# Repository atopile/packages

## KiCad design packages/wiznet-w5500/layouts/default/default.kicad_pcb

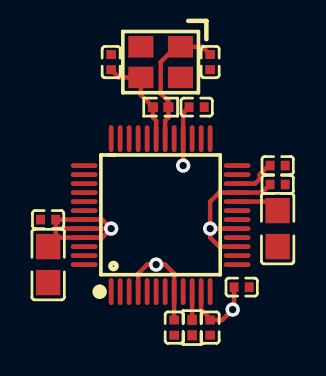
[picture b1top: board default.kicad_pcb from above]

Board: 2 copper layers, 15 parts (0 on the bottom side), 7 nets.

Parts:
C1, C9: 0F; C0805
C2, C3, C4, C5, C6, C7, C8, C10, C11: 0F; C0402
R1: 12400Ω; R0402
R2: 1000000Ω; R0402
U1: LQFP-48_L7.0-W7.0-P0.50-LS9.0-BL
X1: OSC-SMD_4P-L3.2-W2.5-BL_SIT8008BI

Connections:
10: R1.1, U1.10
hv: C1.1, C2.1, C3.1, C4.1, C5.1, C6.1, C7.1, U1.4, U1.8, U1.11, U1.15, U1.17, U1.21, U1.28, U1.43, U1.44, U1.45
lv: C1.2, C2.2, C3.2, C4.2, C5.2, C6.2, C7.2, C8.2, C9.2, C10.2, C11.2, R1.2, U1.3, U1.9, U1.14, U1.16, U1.19, U1.29, U1.48, X1.2, X1.4
p1v2o_cap-power-hv: C8.1, U1.22
tocap_cap-power-hv: C9.1, U1.20
xtal_caps[0]-power-hv: C10.1, R2.1, U1.30, X1.1
xtal_caps[1]-power-hv: C11.1, R2.2, U1.31, X1.3

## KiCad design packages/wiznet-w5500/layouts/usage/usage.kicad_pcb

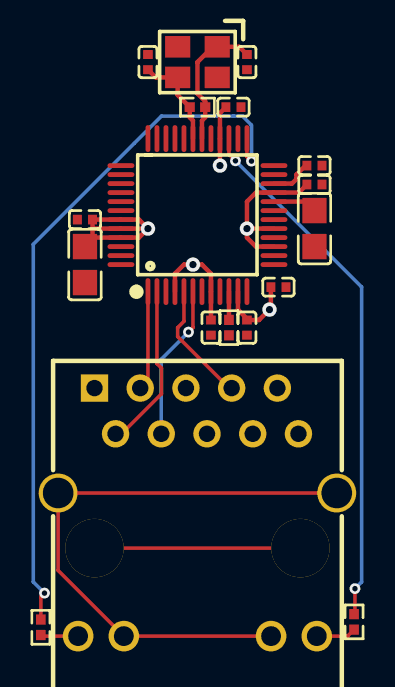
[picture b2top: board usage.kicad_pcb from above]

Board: 2 copper layers, 18 parts (0 on the bottom side), 15 nets.

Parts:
C1, C9: 0F; C0805
C2, C3, C4, C5, C6, C7, C8, C10, C11: 0F; C0402
R1: 12400Ω; R0402
R2: 1000000Ω; R0402
R3, R4: 470Ω; R0402
RJ1: RJ45-TH_HR911130A
U1: LQFP-48_L7.0-W7.0-P0.50-LS9.0-BL
X1: OSC-SMD_4P-L3.2-W2.5-BL_SIT8008BI

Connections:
10: R1.1, U1.10
11: R4.2, RJ1.11
14: R3.2, RJ1.14
W5500_ACT_LED: R3.1, U1.27
W5500_LINK_LED: R4.1, U1.25
W5500_RXN_N: RJ1.P7, U1.5
W5500_RXP_P: RJ1.P4, U1.6
W5500_TXN_N: RJ1.P3, U1.1
W5500_TXP_P: RJ1.P2, U1.2
hv: C1.1, C2.1, C3.1, C4.1, C5.1, C6.1, C7.1, U1.4, U1.8, U1.11, U1.15, U1.17, U1.21, U1.28, U1.43, U1.44, U1.45
lv: C1.2, C2.2, C3.2, C4.2, C5.2, C6.2, C7.2, C8.2, C9.2, C10.2, C11.2, R1.2, RJ1.12, RJ1.13, RJ1.SHIELD0, RJ1.SHIELD1, U1.3, U1.9, U1.14, U1.16, U1.19, U1.29, U1.48, X1.2, X1.4
p1v2o_cap-power-hv: C8.1, U1.22
tocap_cap-power-hv: C9.1, U1.20
xtal_caps[0]-power-hv: C10.1, R2.1, U1.30, X1.1
xtal_caps[1]-power-hv: C11.1, R2.2, U1.31, X1.3

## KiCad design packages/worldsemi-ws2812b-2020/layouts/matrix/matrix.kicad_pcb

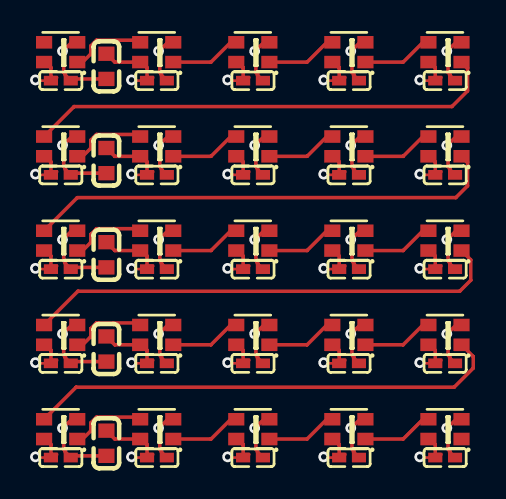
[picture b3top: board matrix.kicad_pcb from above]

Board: 2 copper layers, 55 parts (0 on the bottom side), 26 nets.

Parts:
C1, C7, C13, C19, C25: 10µF ±20% 6.3V X5R; C0603
C2, C3, C4, C5, C6, C8, C9, C10, C11, C12, C14, C15, C16, C17, C18, C20, C21, C22, C23, C24, C26, C27, C28, C29, C30: 100nF ±10% 16V X7R; C0402
LED1, LED2, LED3, LED4, LED5, LED6, LED7, LED8, LED9, LED10, LED11, LED12, LED13, LED14, LED15, LED16, LED17, LED18, LED19, LED20, LED21, LED22, LED23, LED24, LED25: LED-SMD_4P-L2.0-W2.0-TL_WS2812B-2020

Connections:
GND: C1.2, C2.2, C3.2, C4.2, C5.2, C6.2, C7.2, C8.2, C9.2, C10.2, C11.2, C12.2, C13.2, C14.2, C15.2, C16.2, C17.2, C18.2, C19.2, C20.2, C21.2, C22.2, C23.2, C24.2, C25.2, C26.2, C27.2, C28.2, C29.2, C30.2, LED1.2, LED2.2, LED3.2, LED4.2, LED5.2, LED6.2, LED7.2, LED8.2, LED9.2, LED10.2, LED11.2, LED12.2, LED13.2, LED14.2, LED15.2, LED16.2, LED17.2, LED18.2, LED19.2, LED20.2, LED21.2, LED22.2, LED23.2, LED24.2, LED25.2
VCC: C1.1, C2.1, C3.1, C4.1, C5.1, C6.1, C7.1, C8.1, C9.1, C10.1, C11.1, C12.1, C13.1, C14.1, C15.1, C16.1, C17.1, C18.1, C19.1, C20.1, C21.1, C22.1, C23.1, C24.1, C25.1, C26.1, C27.1, C28.1, C29.1, C30.1, LED1.4, LED2.4, LED3.4, LED4.4, LED5.4, LED6.4, LED7.4, LED8.4, LED9.4, LED10.4, LED11.4, LED12.4, LED13.4, LED14.4, LED15.4, LED16.4, LED17.4, LED18.4, LED19.4, LED20.4, LED21.4, LED22.4, LED23.4, LED24.4, LED25.4
leds[1]-data_in-DI-0: LED1.1, LED2.3
leds[1]-data_in-DI-1: LED6.1, LED7.3
leds[1]-data_in-DI-2: LED11.1, LED12.3
leds[1]-data_in-DI-3: LED16.1, LED17.3
leds[1]-data_in-DI-4: LED21.1, LED22.3
leds[2]-data_in-DI-0: LED2.1, LED3.3
leds[2]-data_in-DI-1: LED7.1, LED8.3
leds[2]-data_in-DI-2: LED12.1, LED13.3
leds[2]-data_in-DI-3: LED17.1, LED18.3
leds[2]-data_in-DI-4: LED22.1, LED23.3
leds[3]-data_in-DI-0: LED3.1, LED4.3
leds[3]-data_in-DI-1: LED8.1, LED9.3
leds[3]-data_in-DI-2: LED13.1, LED14.3
leds[3]-data_in-DI-3: LED18.1, LED19.3
leds[3]-data_in-DI-4: LED23.1, LED24.3
leds[4]-data_in-DI-0: LED4.1, LED5.3
leds[4]-data_in-DI-1: LED9.1, LED10.3
leds[4]-data_in-DI-2: LED14.1, LED15.3
leds[4]-data_in-DI-3: LED19.1, LED20.3
leds[4]-data_in-DI-4: LED24.1, LED25.3
strips[1]-data_in-line: LED5.1, LED6.3
strips[2]-data_in-line: LED10.1, LED11.3
strips[3]-data_in-line: LED15.1, LED16.3
strips[4]-data_in-line: LED20.1, LED21.3
